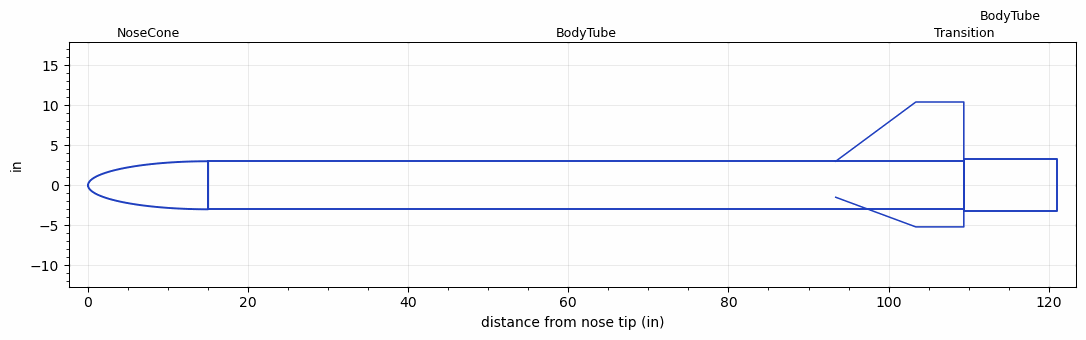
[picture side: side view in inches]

<RASAeroDocument>
 <FileVersion>2</FileVersion>
 <RocketDesign>
  <NoseCone>
   <Length>15</Length>
   <Diameter>6</Diameter>
   <Shape>Elliptical</Shape>
   <Location>0</Location>
  </NoseCone>
  <BodyTube>
   <Length>94.4</Length>
   <Diameter>6</Diameter>
   <Location>15</Location>
   <Fin>
    <Count>3</Count>
    <Chord>16</Chord>
    <Span>7.4</Span>
    <SweepDistance>10</SweepDistance>
    <TipChord>6</TipChord>
    <Thickness>0.1875</Thickness>
    <Location>16</Location>
    <AirfoilSection>Double Wedge</AirfoilSection>
    <FX1>0.125</FX1>
   </Fin>
  </BodyTube>
  <Transition>
   <Length>0.01</Length>
   <Diameter>6.5</Diameter>
   <Location>109.4</Location>
   <RearDiameter>6.5</RearDiameter>
  </Transition>
  <BodyTube>
   <Length>11.6</Length>
   <Diameter>6.5</Diameter>
   <Location>109.41</Location>
  </BodyTube>
  <Surface>Smooth (Zero Roughness)</Surface>
  <ModifiedBarrowman>False</ModifiedBarrowman>
  <Turbulence>False</Turbulence>
  <UseBooster1>False</UseBooster1>
  <UseBooster2>False</UseBooster2>
 </RocketDesign>
 <LaunchSite>
  <Altitude>0</Altitude>
  <Pressure>0</Pressure>
  <RodAngle>0</RodAngle>
  <RodLength>4</RodLength>
  <Temperature>74</Temperature>
  <WindSpeed>0</WindSpeed>
 </LaunchSite>
 <Recovery>
  <Altitude1>1000</Altitude1>
  <Altitude2>1000</Altitude2>
  <DeviceType1>None</DeviceType1>
  <DeviceType2>None</DeviceType2>
  <Event1>False</Event1>
  <Event2>False</Event2>
  <Size1>1</Size1>
  <Size2>1</Size2>
  <EventType1>None</EventType1>
  <EventType2>None</EventType2>
  <CD1>1.33</CD1>
  <CD2>1.33</CD2>
 </Recovery>
</RASAeroDocument>
